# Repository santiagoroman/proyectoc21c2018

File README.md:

# Proyecto Diseño de Circuitos Electrónicos 1C2018

- Documentos de referencia
- Hojas de datos
- Informe
- Simulaciones
- Mediciones

A considerar a la hora de hacer el proyecto:

- [X] Agregar resistencia en la etapa de salida para regulacion termina

- [X] Separar en el PCB las pistas de entrada de las de salida

- [X] Agregar capacitores de 1000uF aprox con la alimentacion de manera tal de no exigir tanto a la fuente

- [X] Asegurarse que el camino de realimentacion (entre salida y entrada al buffer) sea lo más corto posible en el PCB

- [ ] Proteccion de continua en la carga

- [ ] Proteccion de exceso de corriente a la salida (foldback o comun, reusando la resistencia anterior)

Progreso de TP V2.0<br />
<br />
<br />
Tener en cuenta que la vez pasada se nos quemaron muchos BD y TIP, entonces es mejor que solo tenga pistas de un lado. Asi no desoldamos mucho cada vez<br />

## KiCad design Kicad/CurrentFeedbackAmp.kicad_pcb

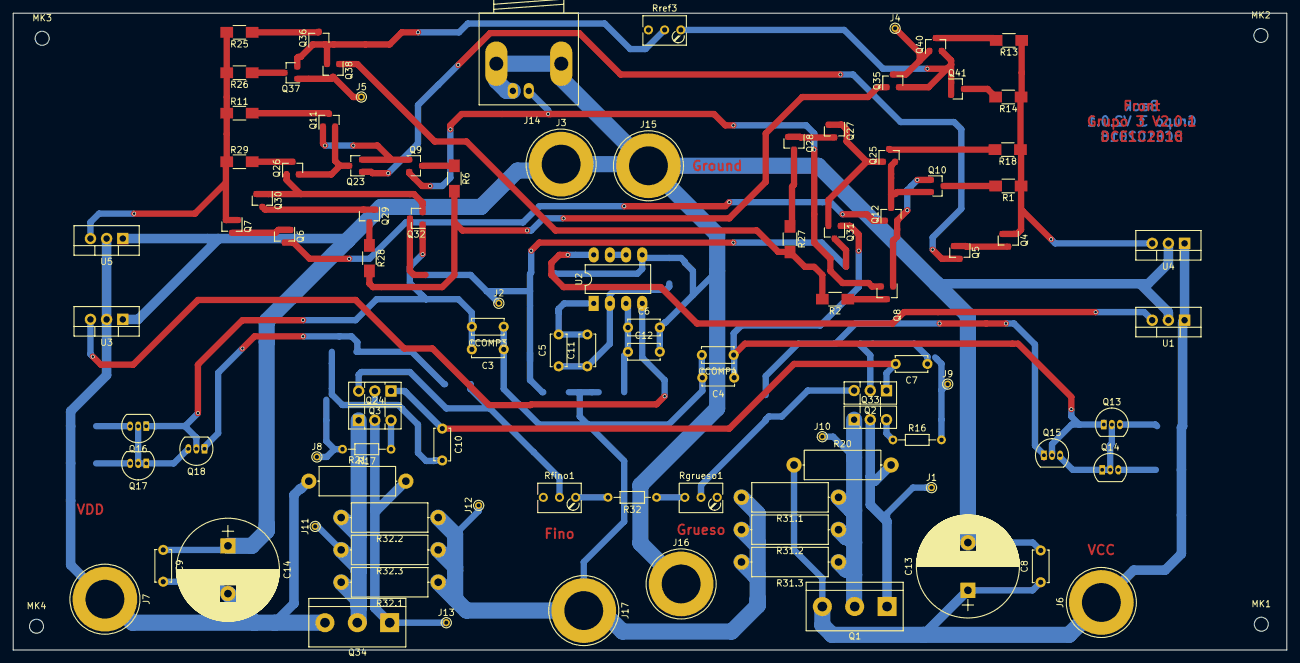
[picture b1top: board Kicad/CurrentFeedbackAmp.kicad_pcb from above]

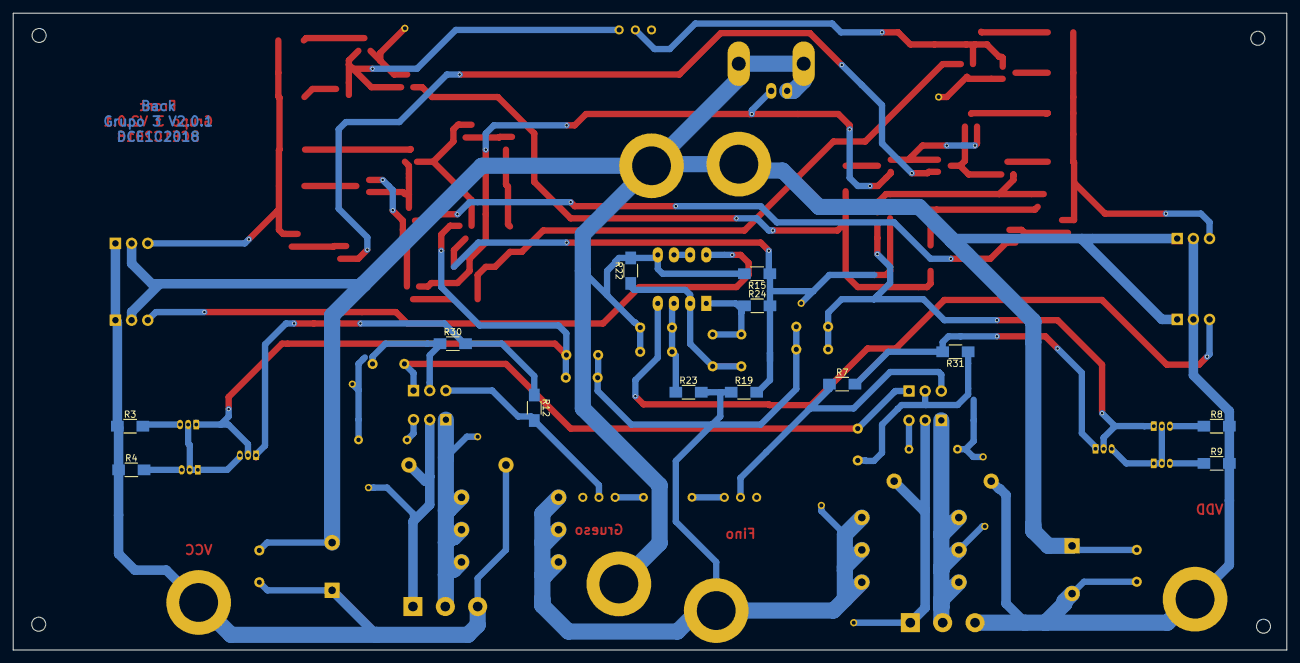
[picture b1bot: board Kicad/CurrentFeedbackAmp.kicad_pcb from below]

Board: 2 copper layers, 200.0 x 100.0 mm, 115 parts (13 on the bottom side), 69 nets.

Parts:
C3, C4: 10p; C_Disc_D5.0mm_W2.5mm_P5.00mm
C5, C6, C11, C12: 470n; C_Disc_D5.0mm_W2.5mm_P5.00mm
C7, C8, C9, C10: 100n; C_Disc_D5.0mm_W2.5mm_P5.00mm
C13, C14: 1000u; CP_Radial_D16.0mm_P7.50mm
CCOMP3, CCOMP4: 10p; C_Disc_D5.0mm_W2.5mm_P5.00mm
J1, J8, J13: Test_Etapa_3_Inf; PINTST
J2: Test_Realim_Out; PINTST
J3: Salida masa1; Banana_Jack_1Pin
J4: Protecc_Sup_Out; PINTST
J5: Protecc_Inf_Out; PINTST
J6: Conector Vcc; Banana_Jack_1Pin
J7: Conector Vdd; Banana_Jack_1Pin
J9: Test_Etapa_3_Sup; PINTST
J10: Protecc_Sup_In1; PINTST
J11: Protecc_Inf_In1; PINTST
J12: Protecc_Sup_In2; PINTST
J14: Entrada; BNC_Socket_TYCO-AMP_LargePads
J15: Salida masa2; Banana_Jack_1Pin
J16: Salida tierra; Banana_Jack_1Pin
J17: Salida senal; Banana_Jack_1Pin
MK1, MK2, MK3, MK4: Mounting_Hole; MountingHole_2.2mm_M2
Q1: TIP42C; TerminalBlock_bornier-3_P5.08mm
Q2, Q33: BD135; TO-126_Vertical
Q3, Q24: BD136; TO-126_Vertical
Q4, Q5, Q8, Q11, Q23, Q26, Q27, Q28, Q31, Q36, Q37, Q38: BC848; SOT-23
Q6, Q7, Q9, Q10, Q12, Q25, Q29, Q30, Q32, Q35, Q40, Q41: BC858; SOT-23
Q13, Q14, Q15: BC559; TO-92_Inline_Narrow_Oval
Q16, Q17, Q18: BC549; TO-92_Inline_Narrow_Oval
Q34: TIP41C; TerminalBlock_bornier-3_P5.08mm
R1, R11, R18, R29: 100; R_1206_HandSoldering
R2, R6, R27, R28: 50; R_1206_HandSoldering
R3, R4, R8, R9: 150; R_1206_HandSoldering
R7, R12: 1k; R_1206_HandSoldering
R13, R14, R25, R26: 200; R_1206_HandSoldering
R15, R24: 330; R_1206_HandSoldering
R16, R17: 50; R_Axial_DIN0204_L3.6mm_D1.6mm_P7.62mm_Horizontal
R19: 3.9k; R_1206_HandSoldering
R20, R21: 100; R_Axial_DIN0414_L11.9mm_D4.5mm_P15.24mm_Horizontal
R22, R23: 100k; R_1206_HandSoldering
R30, R31: 5.1; R_1206_HandSoldering
R31.1, R31.2, R31.3, R32.1, R32.2, R32.3: 1; R_Axial_DIN0414_L11.9mm_D4.5mm_P15.24mm_Horizontal
R32: 1k; R_Axial_DIN0204_L3.6mm_D1.6mm_P7.62mm_Horizontal
Rfino1: POT; Potentiometer_Trimmer_Bourns_3266Y
Rgrueso1: POT; Potentiometer_Trimmer_Bourns_3266Y
Rref3: POT; Potentiometer_Trimmer_Bourns_3266Y
U1: LM7812_TO220; TO-220_Vertical
U2: TL082; DIP-8_W7.62mm_LongPads
U3: LM7912_TO220; TO-220_Vertical
U4: LM7805_TO220; TO-220_Vertical
U5: LM7905_TO220; TO-220_Vertical

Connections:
GND: C6.2, C8.2, C9.1, C12.2, C13.2, C14.1, J3.1, J14.2, J15.1, J16.1, R15.2, R22.2, U1.2, U2.5, U3.1, U4.2, U5.1
Ireference1: Q35.1, R6.2, R28.2
Ireference2: Q38.1, R2.2, R27.2
unnamed: C3.2, CCOMP3.2, Q16.1, Q18.2, Q32.1
unnamed: C4.1, CCOMP4.1, Q13.1, Q15.2, Q31.1
unnamed: C7.1, Q2.2, R30.1
unnamed: C7.2, C10.1, Q2.1, Q3.1
unnamed: C10.2, Q3.2, R31.1
unnamed: C5.1, C11.1, R22.1, U2.2
unnamed: C5.2, C11.2, R24.1, U2.1
unnamed: C6.1, C12.1, R23.1, U2.3
unnamed: J1.1, Q1.1, Q33.2, R20.2
unnamed: J4.1, Q35.3, Q40.1
unnamed: J5.1, Q37.1, Q38.3
unnamed: J8.1, R17.2
unnamed: J9.1, R16.2
unnamed: J10.1, Q1.2, Q33.1, R31.1.1, R31.2.1, R31.3.1
unnamed: J11.1, Q24.1, Q34.2, R32.1.2, R32.2.2, R32.3.2
unnamed: J13.1, Q24.2, Q34.1, R21.2
unnamed: Q2.3, R12.2, Rgrueso1.2
unnamed: Q3.3, R7.1, Rfino1.2
unnamed: Q4.3, Q5.1, Q5.2
unnamed: Q6.1, Q6.2, Q7.3
unnamed: Q8.3, R2.1
unnamed: Q9.3, R6.1
unnamed: Q8.1, Q10.1, Q12.2
unnamed: Q10.2, Q12.3, Q25.2
unnamed: Q10.3, R1.2
unnamed: Q9.1, Q11.1, Q23.2
unnamed: Q11.2, Q23.3, Q26.2
unnamed: Q11.3, R11.2
unnamed: Q6.3, Q12.1
unnamed: Q13.2, Q14.1, Q14.2, Q15.3
unnamed: Q13.3, R3.2
unnamed: Q14.3, R4.2
unnamed: Q15.1, R12.1, R30.2
unnamed: Q16.2, Q17.1, Q17.2, Q18.3
unnamed: Q16.3, R8.1
unnamed: Q17.3, R9.1
unnamed: Q18.1, R7.2, R31.2
unnamed: Q5.3, Q23.1
unnamed: Q24.3, R17.1
unnamed: Q25.1, Q27.1, Q27.2, Q31.2
unnamed: Q25.3, R18.2
unnamed: Q26.1, Q30.1, Q30.2, Q32.2
unnamed: Q26.3, R29.2
unnamed: Q27.3, Q28.1, Q28.2
unnamed: Q28.3, R27.1
unnamed: Q29.1, Q29.2, Q30.3
unnamed: Q29.3, R28.1
unnamed: Q33.3, R16.1
unnamed: Q35.2, Q40.2, Q41.1, Q41.2, Rref3.1
unnamed: Q36.1, Q36.2, Q37.2, Q38.2, Rref3.2
unnamed: Q36.3, R25.1
unnamed: Q37.3, R26.1
unnamed: Q40.3, R13.2
unnamed: Q41.3, R14.2
unnamed: R32.1, Rgrueso1.3
unnamed: R32.2, Rfino1.1
unnamed: U2.6, U2.7
Vcc: C8.1, C13.1, J6.1, Q1.3, R3.1, R4.1, R20.1, U1.1, U4.1
Vcc5: Q4.1, Q4.2, R1.1, R13.1, R14.1, R18.1, U4.3
VccTL: U1.3, U2.8
Vdd: C9.2, C14.2, J7.1, Q34.3, R8.2, R9.2, R21.1, U3.2, U5.2
Vdd5: Q7.1, Q7.2, R11.1, R25.2, R26.2, R29.1, U5.3
VddTL: U2.4, U3.3
Vin+: J14.1, Q8.2, Q9.2
Vin-: J2.1, Q31.3, Q32.3, R15.1, R19.2, R24.2
Vout: C3.1, C4.2, CCOMP3.1, CCOMP4.2, J12.1, J17.1, R19.1, R23.2, R31.1.2, R31.2.2, R31.3.2, R32.1.1, R32.2.1, R32.3.1

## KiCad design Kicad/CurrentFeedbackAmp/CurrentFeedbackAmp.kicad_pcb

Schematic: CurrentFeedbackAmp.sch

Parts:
C1, C2, C3, C4, C5, C6, C8, C9, C11, C12: C; C_Disc_D5.0mm_W2.5mm_P5.00mm
C7, C10: CP; CP_Radial_D8.0mm_P3.80mm
J1: Vin; PINTST
J2: Test_Realim_Out; PINTST
J3: Masa etapa inicial; PINTST
J4: Protecc_Sup_Out; PINTST
J5: Protecc_Inf_Out; PINTST
J6: VccTL; PINTST
J7: VddTL; PINTST
J8: Test_Etapa_3_Inf; PINTST
J9: Test_Etapa_3_Sup; PINTST
J10: Protecc_Sup_In1; PINTST
J11: Protecc_Inf_In1; PINTST
J12: Protecc_Sup_In2; PINTST
J13: Vdd; PINTST
J14: Vcc; PINTST
J15: Masa Filtros; PINTST
J16: Masa Bornera Carga; PINTST
J17: Bornera Carga; TerminalBlock_Pheonix_MKDS1.5-2pol
MK1, MK2, MK3, MK4: Mounting_Hole; MountingHole_2.2mm_M2
Q1: TIP42C; TO-220_Vertical
Q13, Q14, Q15, Q19, Q21, Q35, Q40, Q41, Q42: BC559; TO-92_Inline_Narrow_Oval
Q16, Q17, Q18, Q20, Q22, Q36, Q37, Q38, Q39: BC549; TO-92_Inline_Narrow_Oval
Q24: BD136; TO-126_Vertical
Q33: BD135; TO-126_Vertical
Q34: TIP41C; TO-220_Vertical
R1, R2, R3, R4, R5, R6, R8, R9, R10, R11, R13, R14, R15, R16, R17, R18, R19, R20, R21, R22, R23, R24, R25, R26, R27, R30: R; R_0805_HandSoldering
R31.1, R31.2, R31.3, R32.1, R32.2, R32.3: R; R_Axial_DIN0414_L11.9mm_D4.5mm_P15.24mm_Horizontal
Rref1, Rref2: POT; Potentiometer_Trimmer_Bourns_3266Y
Rref3: POT; Potentiometer_Alps_RK163_Single_Vertical
T1, T2: BC548; TO-92_Inline_Narrow_Oval
U2: TL082; SOIC-8-N

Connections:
DC.servo.Input: C3.1, C4.2, J12.1, J17.1, R19.1, R23.2, R31.1.2, R31.2.2, R31.3.2, R32.1.1, R32.2.1, R32.3.1
DC.servo.Output: J2.1, R1.1, R2.2, R15.1, R19.2, R24.2
GND: C6.2, C7.2, C8.2, C9.1, C10.1, C12.2, J3.1, J15.1, J16.1, J17.2, Q35.1 (C), Q38.1 (C), R15.2, R22.2; also elsewhere on the board
unnamed: C1.1, J9.1, Q19.1 (C), R16.2, Rref2.1, T2.1 (C)
unnamed: C1.2, Q21.3 (E), Rref2.3, T2.3 (E)
unnamed: C2.1, Q20.3 (E), Rref1.1, T1.1 (C)
unnamed: C2.2, J8.1, Q22.1 (C), R17.2, Rref1.3, T1.3 (E)
unnamed: C3.2, Q16.1 (C), Q18.2 (B), Q42.1 (C)
unnamed: C4.1, Q13.1 (C), Q15.2 (B), Q39.1 (C)
unnamed: C7.1, R13.1, R14.1, R30.1
unnamed: C10.2, R25.2, R26.2, R27.1
unnamed: C5.1, C11.1, R22.1, U2.2 (-)
unnamed: C5.2, C11.2, R24.1, U2.1
unnamed: C6.1, C12.1, R23.1, U2.3 (+)
unnamed: J1.1, R6.1, R11.2
unnamed: J4.1, Q35.3 (E), Q39.2 (B), Q40.1 (C)
unnamed: J5.1, Q37.1 (C), Q38.3 (E), Q42.2 (B)
unnamed: J10.1, Q1.2 (C), Q33.1 (E), R31.1.1, R31.2.1, R31.3.1
unnamed: J11.1, Q24.1 (E), Q34.2 (C), R32.1.2, R32.2.2, R32.3.2
unnamed 21: U2.5 (+); also elsewhere on the board
unnamed: Q1.1 (B), Q33.2 (C), R20.2
unnamed: Q13.2 (B), Q14.1 (C), Q14.2 (B), Q15.3 (E), Q19.2 (B)
unnamed: Q13.3 (E), R3.2
unnamed: Q14.3 (E), R4.2
unnamed: Q15.1 (C), Q20.2 (B), R18.1
unnamed: Q16.2 (B), Q17.1 (C), Q17.2 (B), Q18.3 (E), Q22.2 (B)
unnamed: Q16.3 (E), R8.1
unnamed: Q17.3 (E), R9.1
unnamed: Q18.1 (C), Q21.2 (B), R18.2
unnamed: Q19.3 (E), R5.2
unnamed: Q22.3 (E), R10.1
unnamed: Q24.2 (C), Q34.1 (B), R21.2
unnamed: Q24.3 (B), R17.1
unnamed: Q33.3 (B), R16.1
unnamed: Q35.2 (B), R11.1
unnamed: Q36.1 (C), Q36.2 (B), Q37.2 (B), Rref3.2
unnamed: Q36.3 (E), R25.1
unnamed: Q37.3 (E), R26.1
unnamed: Q38.2 (B), R6.2
unnamed: Q39.3 (E), R2.1
unnamed: Q40.2 (B), Q41.1 (C), Q41.2 (B), Rref3.1
unnamed: Q40.3 (E), R13.2
unnamed: Q41.3 (E), R14.2
unnamed: Q42.3 (E), R1.2
unnamed: Rref1.2, T1.2 (B)
unnamed: Rref2.2, T2.2 (B)
unnamed: U2.6 (-), U2.7
Vcc: C8.1, J14.1, Q1.3 (E), Q20.1 (C), R3.1, R4.1, R5.1, R20.1, R30.2; also elsewhere on the board
VccTL: J6.1, U2.4 (V-); also elsewhere on the board
Vdd: C9.2, J13.1, Q21.1 (C), Q34.3 (E), R8.2, R9.2, R10.2, R21.1, R27.2; also elsewhere on the board
VddTL: J7.1, U2.8 (V+); also elsewhere on the board

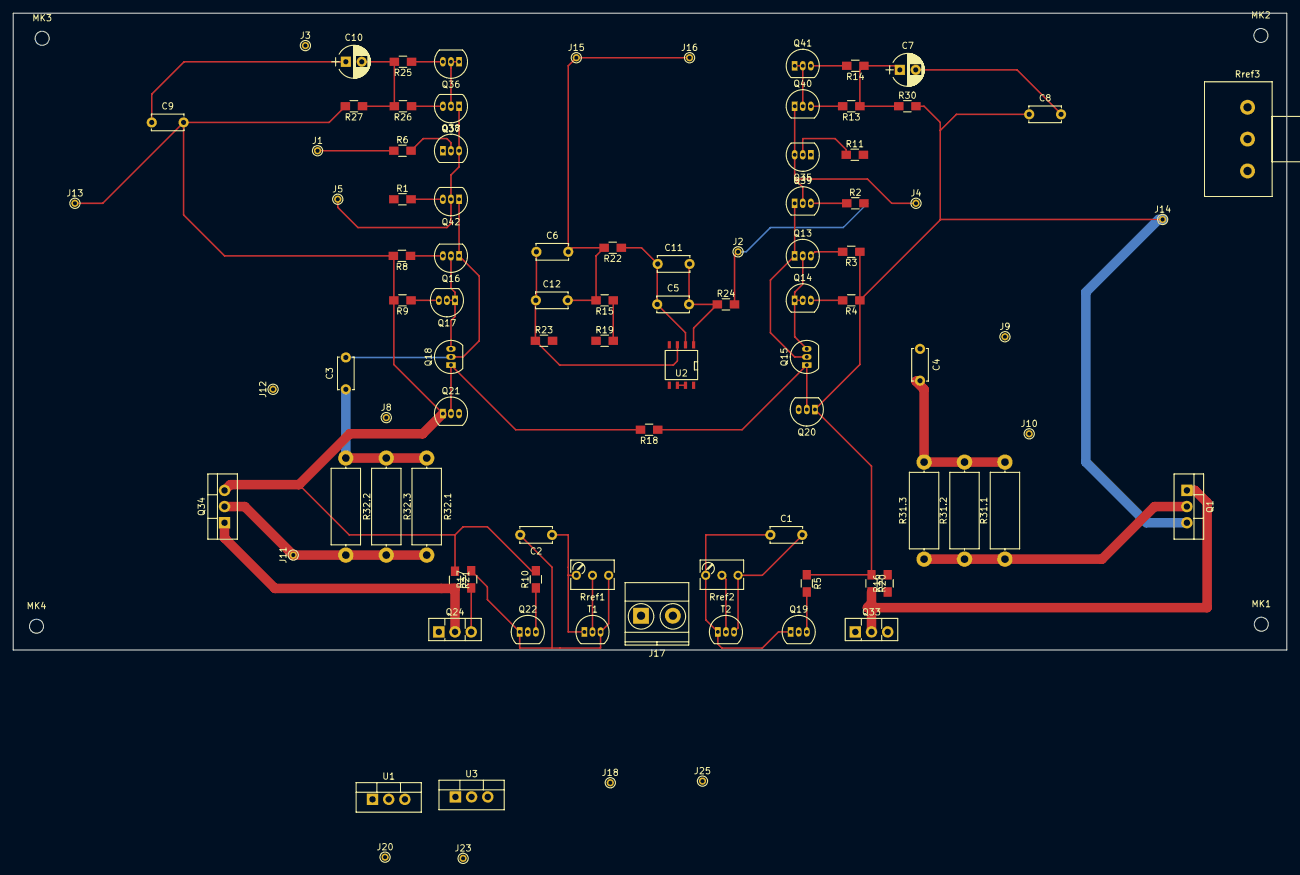
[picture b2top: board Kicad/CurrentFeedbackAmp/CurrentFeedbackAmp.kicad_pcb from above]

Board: 2 copper layers, 200.0 x 100.0 mm, 97 parts (0 on the bottom side), 53 nets.

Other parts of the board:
J18, J20, J23, J25: Masa Reguladores; PINTST
U1: LM7812_TO220; TO-220_Vertical
U3: LM7912_TO220; TO-220_Vertical

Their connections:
GND: J18.1; also elsewhere on the board
unnamed: J20.1, U1.2
unnamed: J23.1, U3.1
unnamed 21: J25.1; also elsewhere on the board
Vcc: U1.1; also elsewhere on the board
VccTL: U1.3; also elsewhere on the board
Vdd: U3.2; also elsewhere on the board
VddTL: U3.3; also elsewhere on the board

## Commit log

2018-05-18 agrego mas docs
2018-05-18 se agrega barra de progresp
2018-05-18 primer bozquejo de circuito
2018-05-19 Primeros documentos auxiliares
2018-05-19 Add basic readme
2018-05-22 se agrega el circuito completo
2018-05-22 agregado libro para servo dc y gitignore para archivos .raw,.net,.log
2018-05-22 barrido frecuencia
2018-05-23 Simulations
2018-05-25 agrego las Especificaciones
2018-05-25 agrego circuito con PseudoDarlington a la salida
2018-05-27 servo dc prueba
2018-05-30 circuito con etapa uno tranca mejorado
2018-05-30 Vamos que se puede!
2018-05-30 tenemos analisis de SNR
2018-06-01 Actualizado con transistores de bajo ruido
2018-06-01 modelos piolas
2018-06-01 Chequeo de Specs
2018-06-02 agrego los cambios en los .lib y las specs que ya cumplimos, falta acomodar lo del pseudo darlington npn para complacer a nuestro querido aquaticci
2018-06-05 ya funciona con 1V de entrada y con 40WRMS
2018-06-05 va la resitencia en el servo
2018-06-05 no quiero poner absolutamente nada
2018-06-05 cambios minimos en el circuito
2018-06-08 va la simulacion de THD
2018-09-10 circuito ahora esta apareado y anda todo, esquematico de kicad apenas empezado
2018-09-10 ancho de banda de potencia THD y compensacion
2018-09-10 Cambios en el servo, but not working yet
2018-09-10 va el TL081
2018-09-10 margen de fase y ancho de banda resuelto-paga
2018-09-10 protecciones que faltan
2018-09-10 todo diez points
2018-09-10 va el circuito con el TL082!
2018-09-10 Circuito casi completo en kicad y testeo de proteccion con foldback
2018-09-10 Ahora si esta el archivo con el prototipo de protecciones
2018-09-10 Va el esquematico de KiCAD con nombres y numeros
2018-09-10 Casi todos los componentes con su respectivo modelo asociado
2018-09-10 va el esquematico incluyendo las resistencias de potencia
2018-09-10 Agregué el borde de la placa
2018-09-10 Alinee los transistores en uno de los extremos del pcb
2018-09-10 Ahora el PCB tiene agujeros para montar la placa y modifique el modelo de los pines
2018-09-10 PCB: Bornera, tierras y nombre a los pines
2018-09-10 Cambio modelo de capacitores electroliticos
2018-09-10 Mas cosas al TODO
2018-09-10 Datasheets y guia para eleccion de borneras
2018-09-10 Configuracion estrella!
2018-09-10 termindado el acomodo de componentes kicad
2018-09-10 algunas pistas
2018-09-10 Kicad compatibility to 4.0.7
2018-09-10 Datasheets de los reguladores de tension para el TL081
2018-09-10 con reguladores para el tl082
2018-09-10 Agregue reguiladores al kicad y complete las conexiones de los pines del tl082
2018-09-10 Conexion correcta de pines inutilizados del TL082 y la guia que explica por que
2018-09-10 Elimine algunos pins que no deberian ir porque van a ser conectados con pistas
2018-09-10 Va la primera etapa de Rooteooooo
2018-09-10 Agregados capacitores de 1000u en sim y kicad, cambié pines de las fuentes de alimentacion por borneras, y puse valores a cada componente
2018-09-10 Actualizo el pcb al releer la netlist para tener los ultimos cambios en el esquematico
2018-09-10 Mejor posicionamiento de componentes, faltan un par de los reguladores
2018-09-10 Agrego archivos fuente de graficos usados en el informe
2018-09-10 Arreglo errores en el README
2018-09-10 Reorganizo el directorio de las simulaciones
2018-09-10 Reorganizo medicion de las simulaciones y README
2018-09-10 se arregla la placa para mejorar la version 1.0
2018-09-10 Reorganizo directorio con archivos de Kicad/PCB
2018-09-10 se actualiza la vista del simalacion
2018-09-12 ya llevamos el esquematico al KiCAD V2.0 Todavia hay que revisar el esquematico
2018-09-17 actualizar
2018-09-17 etapa V3 en el mar la vida es mas sabrosa
2018-09-17 buen ancho de banda mucha amplificacion
2018-09-18 Se agregaron Re a los Amp Dif de la primera etapa
2018-09-19 Armamos con nico el SCH en el KiCAD
2018-09-19 se agrega el pin de entrada, hay que ver si ya podemos empezar con el PCB
2018-09-22 Conectores de tensiones de alimentacion ahora son banana y el conector de la entrada ahora es un BNC hembra
2018-09-22 Modificado conector bornera de salida por dos banana
2018-09-22 Cambiados transistores de fuente de corriente por sus equivalentes SMD
2018-09-22 Cambios en transitores de etapa siguiente a la fuente de corriente por SMD
2018-09-22 Cambiadas resistencias SMD por un modelo SMD que es mas grande asi es mas facil de soldar. Tambier cambiamos las resistencias del cuasidarlington de 100 ohm para que sean THT
2018-09-22 Agregue los modelos para las nuevas resistencias del (ahora unico) multiplicador de Vbe
2018-09-22 Arreglo error en conectores banana de tensiones de alimentacion que tenian el modelo erroneo
2018-09-22 Bug fixing
2018-10-10 movi un par de componentes para despejar la placa
2018-10-13 Empezando la primera etapa. Disenio PCB
2018-10-13 etapa uno terminada, queda mucho lugar para lo demas. Centro reservado para configuracion estrella
2018-10-14 empezando la etapa 2
2018-10-14 fin etapa 2 comienzo etapa tres
2018-10-14 en el READme puse algo que puede sumar a la idea del circuitp
2018-10-15 Todos los componentes colocados en la placa, faltan hacer mejoras pero al menos demuestra que es posible terminarla :D
2018-10-15 Arreglo una conexion a los TL que estaba en la capa frontal pero tenia que ir en la trasera (ese truquito solo sirve para capacitores y resistencias tht)
2018-10-15 Algunas conexiones mas, incluida la de retorno de masa que va por el "medio" de la placa
2018-10-16 Avance con ensanchado, acomodado de pistas y reposicionamiento de los LM
2018-10-17 Configuracion estrella
2018-10-18 1 Unconnected, let the game begin
2018-10-18 Ultima conexion hecha, era un pedacito practicamente invisible...
2018-10-18 mover capacitores de SlewRate
2018-10-28 reparacion version vieja vs nueva de Kicad. Si van a hacer algo gratuito y libre por lo menos haganlo bien!
2018-10-29 Reestructuracion total, fede mode
2018-10-29 ya esta colocado los potes de VBE mejoramos posicion de realimentacion
2018-10-29 va la primera version con Kicad 5
2018-10-30 Etapa de potencia, distancia minima entre pistas
2018-11-04 Me falta solo conectar uno
2018-11-04 Modifique algunas conexiones en transistores para que la conexion en si entre pista y transitor sea en el back en vez del front, obviamente que para lograrlo tuve que agregar algunas vias mas
2018-11-04 Primer intento de unir la ultima conexion
2018-11-04 Mejoras en dos caminos para evitar que se solapen con otras pistas
2018-11-04 Se agregan textos para saber mejor los puntos importantes
2018-11-04 Mayor separacion entre J16 y J17 por seguridad y reactive las diferentes capas
2018-11-04 Arreglue posicion de los transistores de salida
2018-11-05 Mala mia, al final estaba bien el sentido de los transistores de salida asi que vuelvo atras
2018-11-06 Movimos para arriba los transistores del multiplicador asi podemos llegar a tener una unica chapita
2018-11-06 Ya va quedando mucho mas prolijo y mas parecido a un amplificador de audio pro
2018-11-06 ya podemos armar la placa!
2018-12-14 van dos hojas de datos
2019-02-08 Esquematico de Kicad actualizado
2019-02-08 Resistencias y Capacitor entre primera y segunda etapas
2019-02-09 Simulacion cambiada, del multiplicador directo al cuasi
2019-02-09 me habia olvidado de guardar con el ultimo valor de las R a 1K del mult de Vbe
2019-02-10 Se modificó levemente la ganancia para cumplir la spec ahora que se removieron Q19,20, 21 y 22
2019-02-11 Aumentamos resistencia de seguridad y cambios en resistencia de realimentacion
2019-02-20 va el circuito sin muchas cosas que sobraban
2019-02-21 Simulacion con posible proteccion + doc que explica protecciones
2019-02-21 datasheets protecciones
2019-02-21 datasheet 555 mejor
